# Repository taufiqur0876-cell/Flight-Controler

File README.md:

# Flight Controller

Proyek pembuatan **flight controller** (pengendali penerbangan) untuk wahana terbang, dirancang dari nol mulai dari skematik hingga desain PCB.

## Status

🚧 **Dalam pengembangan** — saat ini berada di tahap perancangan skematik dan layout PCB.

## Gambaran Singkat

Flight controller ini dirancang sebagai papan kendali utama yang mengatur pembacaan sensor, pemrosesan data, dan keluaran kendali ke aktuator. Desain dibagi menjadi beberapa blok rangkaian:

- **Mikrokontroler utama** beserta rangkaian pendukung (clock/kristal, reset, boot)
- **Manajemen daya** (regulator tegangan)
- **Antarmuka komunikasi** (USB dan modul nirkabel)
- **Antarmuka sensor**
- **Driver keluaran** untuk motor/aktuator
- **Konektor I/O** untuk perangkat eksternal

## Isi Repositori

| Folder / File | Keterangan |
|---|---|
| `schematic/` | File skematik rangkaian |
| `pcb/` | File desain layout PCB |
| `docs/` | Dokumentasi dan catatan perancangan |

## Rencana Pengembangan

- [x] Perancangan skematik
- [ ] Penyelesaian routing PCB
- [ ] Design Rule Check (DRC) dan review
- [ ] Fabrikasi PCB
- [ ] Perakitan dan pengujian hardware
- [ ] Pengembangan firmware

## Catatan

Proyek ini masih berjalan, sehingga desain dan struktur repositori dapat berubah sewaktu-waktu.

## Penulis

Taufiqur Rahman — Politeknik Elektronika Negeri Surabaya (PENS)

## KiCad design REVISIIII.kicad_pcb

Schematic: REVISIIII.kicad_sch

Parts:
BT2: BS-2450; BAT_BS-2450
C1, C2, C39, C40: 10uf; C_0805_2012Metric_Pad1.18x1.45mm_HandSolder
C3, C41, C47: 0.1uf; C_0805_2012Metric_Pad1.18x1.45mm_HandSolder
C4, C5: C_Polarized; C_3640_9110Metric_Pad2.10x10.45mm_HandSolder
C6, C8: 100uf; C_3640_9110Metric_Pad2.10x10.45mm_HandSolder
C7, C9: 220uf; C_3640_9110Metric_Pad2.10x10.45mm_HandSolder
C10, C11, C33, C34, C49, C50, C51, C52, C53, C54, C55, C56, C57, C58, C59, C61, C62, C63, C64, C74: C; C_0805_2012Metric_Pad1.18x1.45mm_HandSolder
C13, C20, C22, C23, C26, C27, C43, C45, C46, C60, C65, C67, C68, C71: 0.1uF; C_0805_2012Metric_Pad1.18x1.45mm_HandSolder
C14, C15, C16, C17, C28, C29, C30, C31, C37, C38: TBD; C_0805_2012Metric_Pad1.18x1.45mm_HandSolder
C18: 1DnF; C_0805_2012Metric_Pad1.18x1.45mm_HandSolder
C19, C21, C24, C42, C44, C66, C69, C72: 1uF; C_0805_2012Metric_Pad1.18x1.45mm_HandSolder
C25, C70, C73: 10uF; C_0805_2012Metric_Pad1.18x1.45mm_HandSolder
C32: NC; C_0805_2012Metric_Pad1.18x1.45mm_HandSolder
C35, C36: 12pF; C_0805_2012Metric_Pad1.18x1.45mm_HandSolder
C48: 470nF; C_0805_2012Metric_Pad1.18x1.45mm_HandSolder
D1, D2, D3, D5, D7, D9, D11, D13, D17, D20, D23: LED; LED_0201_0603Metric
D4, D6, D8, D10, D12, D14: 1N4148WT; D_SOD-523
D15, D16, D18, D19, D21, D22: SS38; D_SMA
D24: ESD9B3.3ST5G; D_SOD-923
IC3: PSM712-LF-T7; PSM712LFT7; Manufacturer_Part_Number PSM712-LF-T7
J1, J2, J3, J4, J5, J6: Screw_Terminal_01x03; TerminalBlock_MaiXu_MX126-5.0-03P_1x03_P5.00mm
J7, J8, J9, J10, J11, J12, J14: Conn_01x02_Pin; PhoenixContact_SPT_1.5_2-H-3.5_1x02_P3.5mm_Horizontal
J15, J18: USB_C_Receptacle_USB2.0_16P; USB_C_Receptacle_HRO_TYPE-C-31-M-12
J16, J17, J19: RSP-122811-01; SAMTEC_RSP-122811-01
K1, K2, K3, K4, K5, K7: SRD-05VDC-SL-C; RELAY_SRD-05VDC-SL-C
L1, L2, L3, L4, L6, L7, L9, L10, L12, L13, L15, L18: L; L_Neosid_SM-PIC0512H
L5: 2,0nH 500mA; L_Neosid_SM-PIC0512H
L8: NC; L_Neosid_SM-PIC0512H
L11, L14, L16: 15uH; L_Neosid_SM-PIC0512H
L17: 20nH; L_Neosid_SM-PIC0512H
MICRO_SD1: TF-01A; TF-01A_snapEda
Q1, Q3, Q4, Q5, Q6, Q9: MMBT2222_; SOT23-BEC
Q7: 2N7002BKSH; SOT65P210X110-6N; Manufacturer_Part_Number 2N7002BKSH; Mouser Part Number 771-2N7002BKSH
Q8: SS8050; SOT-23
R1, R2, R3, R4, R5, R6, R7, R8, R9, R10, R11, R12, R13, R14: 330; R_0201_0603Metric
R15, R16, R17, R51: R; R_0201_0603Metric
R18: 120R; R_0201_0603Metric
R19, R20: 360R; R_0201_0603Metric
R21, R22, R23, R24: R_0201_0603Metric
R28, R29, R42, R43: 5.1K; R_0201_0603Metric
R30, R31: 33R; R_0201_0603Metric
R32, R33, R34, R47, R48, R58: 10K; R_0201_0603Metric
R35: DNP; R_0201_0603Metric
R36, R55: 499; R_0201_0603Metric
R37, R38, R39, R40, R41: 0; R_0201_0603Metric
R44, R56, R57: 4K7; R_0201_0603Metric
R45, R46, R49, R52, R53, R54: 0R; R_0201_0603Metric
R50: 10R; R_0201_0603Metric
SW1, SW2, SW3: SW_Push; SW_Tactile_Straight_KSA0Axx1LFTR
SW4, SW5: 1825910-6; SW_1825910-6-4; PARTREV C10
U1, U13: AMS1117-3.3; SOT-223-3_TabPin2
U2, U3, U4, U5, U6, U7: PC817; DIP-4_W7.62mm
U8, U9, U10: LM2596S-ADJ; TO-263-5_TabPin3
U11: W25Q128JVSIQ; SOIC127P790X216-8N; PARTREV I
U12: ESP32-S3; IC_ESP32-S3; PARTREV v1.2
U14: CP2102-GM; QFN50P500X500X100-29N; PARTREV 1.8
U15: SX1262IMLTRT; QFN50P400X400X100-25N; PARTREV 1.1
U16: UPG2179TB; SUPER_MINIMOLD
U17: ESP32-S3FN8; QFN40P700X700X90-57N; DigiKey_Part_Number 1965-ESP32-S3FN8CT-ND
U18: DS1307Z_; SOIC127P600X175-8N
U19: MAX3485EESA_; SOIC127P600X175-8N
Y2, Y5: Crystal_GND24; Crystal_SMD_SeikoEpson_FA128-4Pin_2.0x1.6mm
Y3, Y4, Y7: Crystal; Crystal_SMD_3215-2Pin_3.2x1.5mm
Y6: TX32-33010S-32.000-X-R; OSC_TX32-33010S-32.000-X-R; PARTREV Nov 07, 2023

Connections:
5V RELAY: C4.1, D4.1 (K), D4.2 (A), D6.1 (K), D6.2 (A), D8.1 (K), D8.2 (A), D10.1 (K), D10.2 (A), D12.1 (K), D12.2 (A), D14.1 (K), D14.2 (A), J8.2, K1.A1, K1.A2, K2.A1, K2.A2, K3.A1, K3.A2, K4.A1, K4.A2, K5.A1, K5.A2, K7.A1, K7.A2, L1.2, Q1.C, Q3.C, Q4.C, Q5.C, Q6.C, Q9.C, R3.1, R5.1, R7.1, R9.1, R11.1, R13.1, R15.1, U2.4, U3.4, U4.4, U5.4, U6.4, U7.4, U8.4 (FB); also elsewhere on the board
+3.3V: C9.1, C10.1, C11.1, C18.1, C19.1, C23.1, C24.1, C25.1, C26.1, C27.1, C60.1, C65.1, C68.1, C69.1, C70.1, J12.2, L3.2, L5.2, L17.2, MICRO_SD1.4 (VDD), R17.1, R19.2, R21.1, R22.1, R23.1, R24.2, R32.1, R33.1, R34.1, R35.2, R45.2, R46.1, R47.1, R48.1, R54.2, U10.4 (FB), U12.20 (VDD3P3_RTC), U12.46 (VDD3P3_CPU), U12.55 (VDDA1), U12.56 (VDDA2), U15.1 (VDD_IN), U17.20 (VDD3P3_RTC), U17.46 (VDD3P3_CPU)
+5V: C7.1, C43.1, C44.1, J10.2, L2.2, R16.1, R44.1, R56.2, R57.2, R58.2, U9.4 (FB), U14.7 (REGIN), U14.8 (VBUS), U18.8 (VCC)
ANT SW: R52.1, R53.1, U15.12 (DIO2)
BTN: R34.2, SW3.1, U12.19 (GPIO14)
CHIP PU LORA: C45.1, C46.1, Q7.6 (D1), R46.2, SW5.3, SW5.4, U17.4 (CHIP_PU)
CHIP-PU: C13.1, R32.2, SW1.1, U12.4 (CHIP_PU)
CS SD CARD: MICRO_SD1.2 (CD/DAT3), R24.1
DIO1: U15.13 (DIO1)
DTR: C45.2, Q7.2 (G1), Q7.4 (S2), U14.28 (~DTR)
D_N: J18.A7 (D-), J18.B7 (D-), U14.5 (D–)
D_P: J18.A6 (D+), J18.B6 (D+), U14.4 (D+)
FLASH: R33.2, SW2.1, U12.5 (GPIO0)
GPIO0 LORA: U17.5 (GPIO0)
GPIO1: R2.1, U12.6 (GPIO1)
GPIO1 LORA: U17.6 (GPIO1)
GPIO2: U12.7 (GPIO2)
GPIO2 LORA: U17.7 (GPIO2)
GPIO3: U12.8 (GPIO3)
GPIO3 LORA: U17.8 (GPIO3)
GPIO4: U12.9 (GPIO4)
GPIO4 LORA: U17.9 (GPIO4)
GPIO5: U12.10 (GPIO5)
GPIO5 LORA: U17.10 (GPIO5)
GPIO6: U12.11 (GPIO6)
GPIO6 LORA: U17.11 (GPIO6)
GPIO7: U12.12 (GPIO7)
GPIO7 LORA: U17.12 (GPIO7)
GPIO8: U12.13 (GPIO8)
GPIO8 LORA: R47.2, U15.19 (NSS), U17.13 (GPIO8)
GPIO9: U12.14 (GPIO9)
GPIO9 LORA: U15.18 (SCK), U17.14 (GPIO9)
GPIO10: U12.15 (GPIO10)
GPIO10 LORA: U15.17 (MOSI), U17.15 (GPIO10)
GPIO11: U12.16 (GPIO11)
GPIO11 LORA: U15.16 (MISO), U17.16 (GPIO11)
GPIO12: U12.17 (GPIO12)
GPIO12 LORA: R48.2, U15.15 (~NRESET), U17.17 (GPIO12)
GPIO13: U12.18 (GPIO13)
GPIO13 LORA: U15.14 (BUSY), U17.18 (GPIO13)
GPIO14 LORA: U17.19 (GPIO14)
GPIO17: U12.23 (GPIO17)
GPIO17 LORA: U17.23 (GPIO17)
GPIO18: U12.24 (GPIO18)
GPIO18 LORA: U17.24 (GPIO18)
GPIO19: R30.2, U12.25 (GPIO19)
GPIO19 LORA: U17.25 (GPIO19)
GPIO20: R31.2, U12.26 (GPIO20)
GPIO20 LORA: U17.26 (GPIO20)
GPIO21: U12.27 (GPIO21)
GPIO21 LORA: U17.27 (GPIO21)
GPIO33: U12.38 (GPIO33)
GPIO33 LORA: U17.38 (GPIO33)
GPIO34: U12.39 (GPIO34)
GPIO34 LORA: U17.39 (GPIO34)
GPIO35: U12.40 (GPIO35)
GPIO35 LORA: U17.40 (GPIO35)
GPIO36: U12.41 (GPIO36)
GPIO36 LORA: U17.41 (GPIO36)
GPIO37: U12.42 (GPIO37)
GPIO37 LORA: U17.42 (GPIO37)
GPIO38: U12.43 (GPIO38)
GPIO38 LORA: U17.43 (GPIO38)
GPIO39: U12.44 (MTCK)
GPIO40: U12.45 (MTDO)
GPIO41: U12.47 (MTDI)
GPIO42: U12.48 (MTMS)
GPIO45: R35.1, U12.51 (GPIO45)
GPIO45 LORA: U17.51 (GPIO45)
GPIO46: U12.52 (GPIO46)
GPIO46 LORA: U17.52 (GPIO46)
GPIO47: U12.37 (SPICLK_P)
GPIO48: U12.36 (SPICLK_N)
GPIO 26 LORA: U17.28 (SPICS1)
GPIO 39 LORA: U17.44 (MTCK)
GPIO 40 LORA: U17.45 (MTDO)
GPIO 41 LORA: U17.47 (MTDI)
GPIO 42 LORA: U17.48 (MTMS)
GPIO 47 LORA: U17.37 (SPICLK_P)
GPIO 48 LORA: U17.36 (SPICLK_N)
IN RELAY 1: D5.1 (K)
IN RELAY 2: D3.1 (K)
IN RELAY 3: D7.1 (K)
IN RELAY 4: D9.1 (K)
IN RELAY 5: D11.1 (K), D13.1 (K)
LNA_IN LORA: C34.1, L9.2, U17.1 (LNA_IN)
MISO SD CARD: MICRO_SD1.7 (DAT0), R23.2
MOSI SD CARD: MICRO_SD1.3 (CMD), R21.2
NC1: J2.3, K2.NC
NC2: J1.3, K7.NC
NC3: J3.3, K1.NC
NC4: J4.3, K3.NC
NC5: J5.3, K5.NC
NC6: J6.3, K4.NC
NO1: J2.1, K2.NO
NO2: J1.1, K7.NO
NO3: J3.1, K1.NO
NO4: J4.1, K3.NO
NO5: J5.1, K5.NO
NO6: J6.1, K4.NO
unnamed: C15.1, L4.1, Y2.3
unnamed: C29.1, C30.1, L6.1, L7.2
unnamed: C32.1, L8.1
unnamed: C33.1, J17.1, L8.2, L9.1
unnamed: C38.1, L10.1, Y5.3
unnamed: C51.1, C53.1, L12.2, L13.1, R51.2
unnamed: C52.1, C53.2, L13.2, L14.1
unnamed: C54.1, L14.2
unnamed: C59.1, C63.1, L16.1
unnamed: C64.1, J19.1, L16.2
unnamed: D1.2 (A), R1.2
unnamed: D2.2 (A), R2.2
unnamed: D3.2 (A), U2.2
unnamed: D5.2 (A), U3.2
unnamed: D7.2 (A), U4.2
unnamed: D9.2 (A), U5.2
unnamed: D11.2 (A), U6.2
unnamed: D13.2 (A), U7.2
unnamed: D15.1 (K), L1.1, U8.2 (OUT)
unnamed: D16.2 (A), J7.1
unnamed: C5.1, D16.1 (K), U8.1 (VIN)
unnamed: D17.2 (A), R15.2
unnamed: D18.2 (A), J9.1
unnamed: C6.1, D18.1 (K), U9.1 (VIN)
unnamed: D19.1 (K), L2.1, U9.2 (OUT)
unnamed: D20.2 (A), R16.2
unnamed: D21.2 (A), J11.1
unnamed: C8.1, D21.1 (K), U10.1 (VIN)
unnamed: D22.1 (K), L3.1, U10.2 (OUT)
unnamed: D23.2 (A), R17.2
unnamed: C31.1, D24.2 (A2), J16.1, L7.1
unnamed: IC3.1 (I/O_1), J14.2, R18.1, R20.2, U19.7 (B)
unnamed: IC3.2 (I/O_2), J14.1, R18.2, R19.1, U19.6 (A)
unnamed: J1.2, K7.COM
unnamed: J2.2, K2.COM
unnamed: J3.2, K1.COM
unnamed: J4.2, K3.COM
unnamed: J5.2, K5.COM
unnamed: J6.2, K4.COM
unnamed: J15.A5 (CC1), R28.1
unnamed: J15.B5 (CC2), R29.1
unnamed: J15.A6 (D+), J15.B6 (D+), R31.1
unnamed: J15.A7 (D-), J15.B7 (D-), R30.1
unnamed: J18.A5 (CC1), R42.1
unnamed: J18.B5 (CC2), R43.1
unnamed: J19.G1, J19.G2
unnamed: Q1.B, R8.2
unnamed: Q3.B, R10.2
unnamed: Q4.B, R12.2
unnamed: Q5.B, R14.2
unnamed: Q6.B, R6.2
unnamed: Q7.3 (D2), R45.1, SW4.3, SW4.4
unnamed: Q8.1 (B), R53.2
unnamed: Q9.B, R4.2
unnamed: R3.2, U2.1
unnamed: R4.1, U2.3
unnamed: R5.2, U3.1
unnamed: R6.1, U3.3
unnamed: R7.2, U4.1
unnamed: R8.1, U4.3
unnamed: R9.2, U5.1
unnamed: R10.1, U5.3
unnamed: R11.2, U6.1
unnamed: R12.1, U6.3
unnamed: R13.2, U7.1
unnamed: R14.1, U7.3
unnamed: C28.1, L6.2, U12.1 (LNA_IN)
unnamed: R39.1, U12.33 (SPICLK)
unnamed: R41.1, U12.35 (SPID)
unnamed: R37.1, U12.30 (SPIHD)
unnamed: R40.1, U12.34 (SPIQ)
unnamed: R38.1, U12.31 (SPIWP)
unnamed: R36.1, U12.49 (U0TXD)
unnamed: C42.1, U14.6 (VDD)
unnamed: R44.2, U14.9 (~RST)
unnamed: L11.2, U15.9 (DCC_SW)
unnamed: R50.2, U15.6 (DIO3)
unnamed: R51.1, U15.23 (RFO)
unnamed: C48.1, L11.1, U15.7 (VREG)
unnamed: C49.1, C50.1, L12.1, U15.24 (VR_PA)
unnamed: R49.1, U15.3 (XTA)
unnamed: C63.2, U16.2 (GND)
unnamed: C61.2, U16.1 (OUT1)
unnamed: C62.2, R52.2, U16.3 (OUT2)
unnamed: C54.2, C55.1, U16.6 (VC1)
unnamed: C57.1, C58.2, U16.4 (VC2)
unnamed: R55.2, U17.49 (U0TXD)
unnamed: C66.1, C73.1, U17.55 (VDDA1), U17.56 (VDDA2)
unnamed: L18.2, U17.54 (XTAL_P)
unnamed: R58.1, U18.7 (SQW/OUT)
unnamed: BT2.+, U18.3 (VBAT)
unnamed: U18.2 (X2), Y7.1
unnamed: R49.2, Y6.1 (NC/GND)
unnamed: C47.1, R50.1, Y6.4 (VDC)
RE DE RS485: U19.2 (~RE), U19.3 (DE)
RFI_N: C57.2, L15.2, U15.22 (RFI_N)
RFI_P: C56.2, L15.1, U15.21 (RFI_P)
RTS: Q7.1 (S1), Q7.5 (G2), U14.24 (~RTS)
RX: U12.50 (U0RXD)
RX RS485: U19.1 (RO)
SCK SD CARD: MICRO_SD1.5 (CLK), R22.2
SCL RTC: R57.1, U18.6 (SCL)
SDA RTC: R56.1, U18.1 (X1), U18.5 (SDA), Y7.2
SHIELD: MICRO_SD1.MP1 (SHIELD), MICRO_SD1.MP2 (SHIELD), MICRO_SD1.MP3 (SHIELD), MICRO_SD1.MP4 (SHIELD)
SPICLK: R39.2, U11.6 (CLK)
SPICS0: U11.1 (/CS)
SPICS1: U12.28 (SPICS1)
SPICSO: U12.32 (SPICS0)
SPID: R41.2, U11.5 (DI(IO0))
SPIHD: R37.2, U11.7 (/HOLD/RESET(IO3))
SPIQ: R40.2, U11.2 (DO(IO1))
SPIWP: R38.2, U11.3 (/WP(IO2))
TX: R36.2
TX RS485: U19.4 (DI)
UORX LORA: R55.1, U14.26 (TXD), U17.50 (U0RXD)
UOTX LORA: U14.25 (RXD)
V USB: C2.1, J15.A4 (VBUS), J15.A9 (VBUS), J15.B4 (VBUS), J15.B9 (VBUS), U1.3 (VI)
V USB LORA: J18.A4 (VBUS), J18.A9 (VBUS), J18.B4 (VBUS), J18.B9 (VBUS)
VC1: Q8.3 (C), R54.1
VCC: C1.1, C3.1, C40.1, C41.1, C74.1, R1.1, U1.2 (VO), U13.2 (VO), U19.8 (VCC)
VDD SPI: C20.1, C21.1, U11.8 (VCC), U12.29 (VDD_SPI)
VDD_SPI_LORA: C71.1, C72.1, U17.29 (VDD_SPI)
VUSB LORA: C39.1, U13.3 (VI)
XTAL_32KN LORA: C35.1, U17.22 (XTAL_32K_N), Y4.1
XTAL_32KP LORA: C36.1, U17.21 (XTAL_32K_P), Y4.2
XTAL_32N: C17.1, U12.22 (XTAL_32K_N), Y3.1
XTAL_32P: C16.1, U12.21 (XTAL_32K_P), Y3.2
XTAL_N: C14.1, U12.53 (XTAL_N), Y2.1
XTAL_N LORA: C37.1, U17.53 (XTAL_N), Y5.1
XTAL_P: L4.2, U12.54 (XTAL_P)
XTAL_P LORA: L10.2, L18.1

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
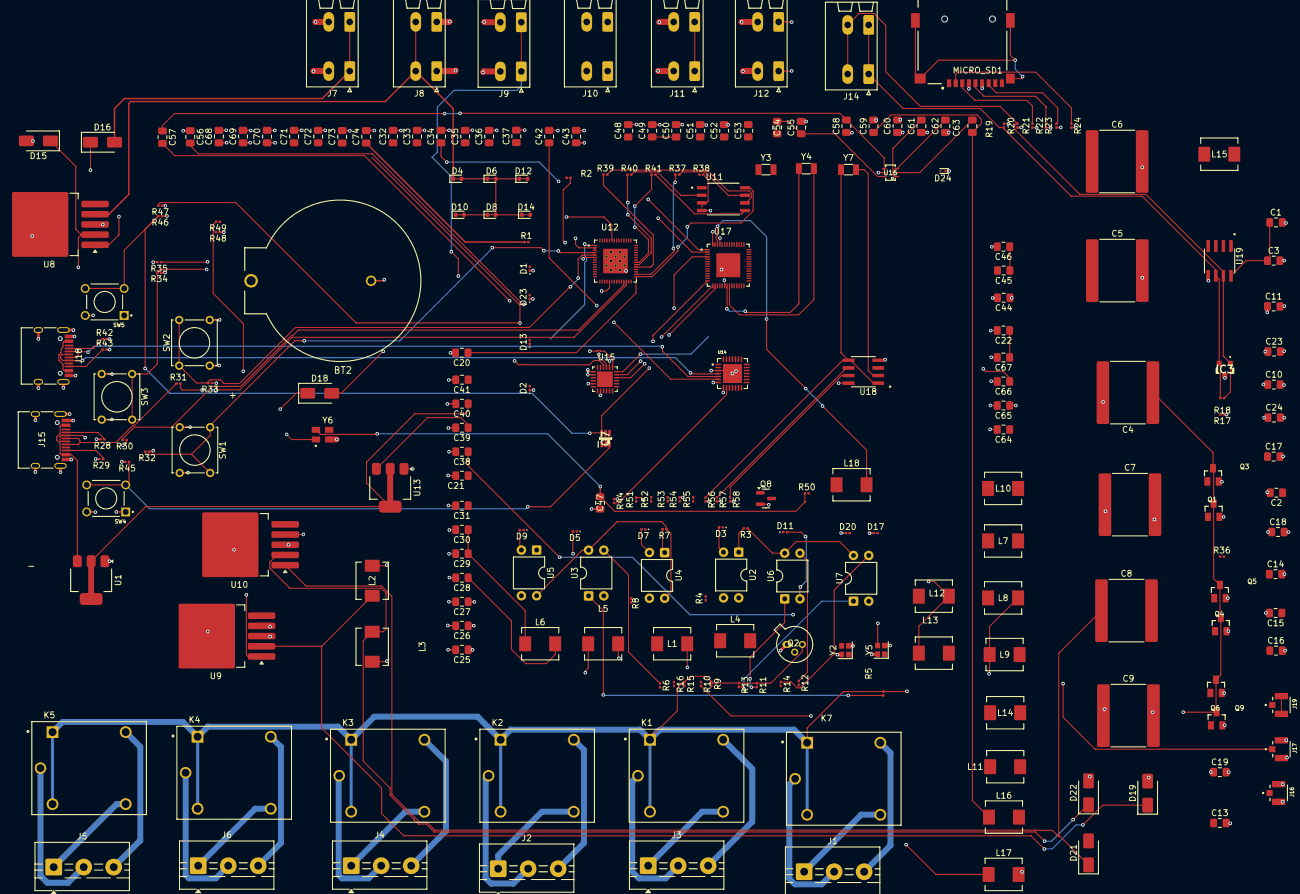
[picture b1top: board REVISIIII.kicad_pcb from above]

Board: 4 copper layers, 236 parts (0 on the bottom side), 163 nets.

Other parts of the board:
Q2: BC107; TO-18-3

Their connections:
5V RELAY: Q2.3 (C); also elsewhere on the board
